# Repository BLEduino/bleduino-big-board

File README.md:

Big-Board
=========

The BLEduinos test board used to verify and test the individual components on the final BLEduino.

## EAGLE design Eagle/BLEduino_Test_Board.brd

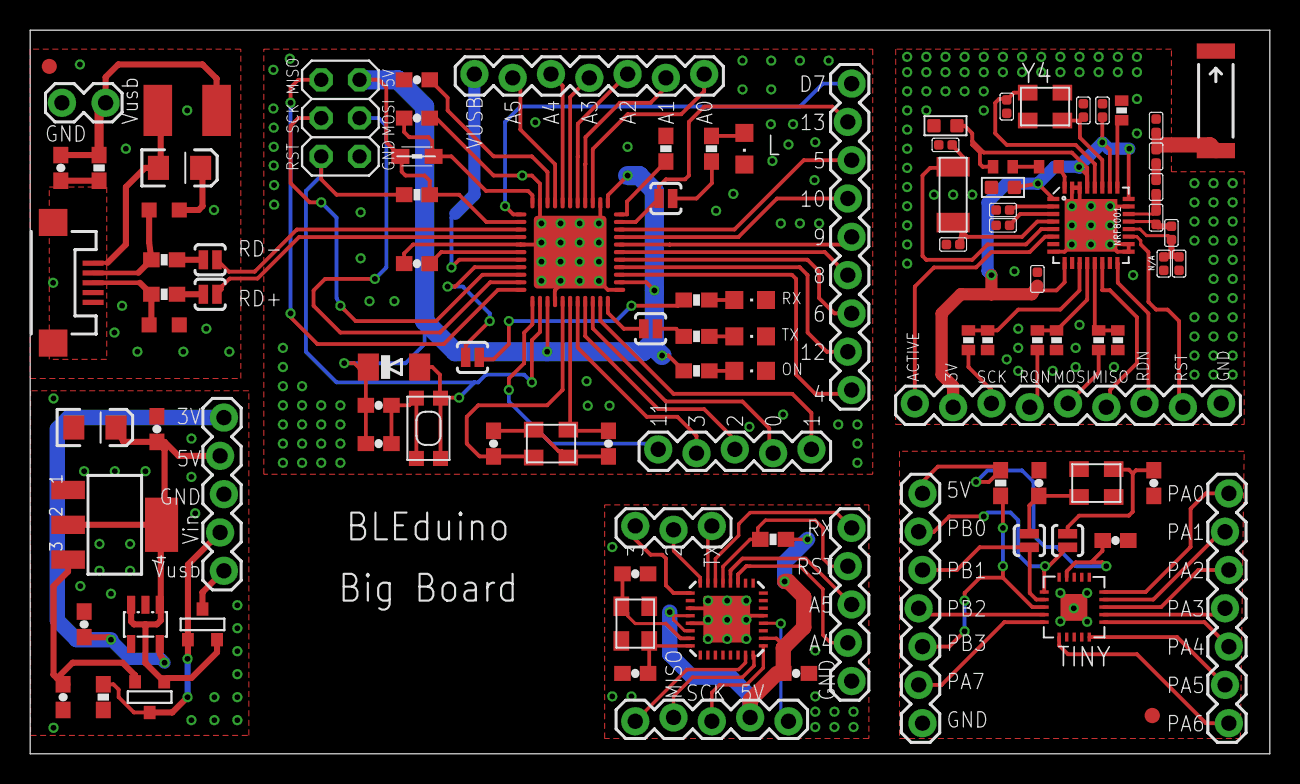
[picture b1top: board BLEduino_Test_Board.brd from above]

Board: 4 copper layers, 82.2 x 48.0 mm, 103 parts (0 on the bottom side), 114 nets.

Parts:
32.768KHZ: FITNESSDEVICE_CRYSTAL-ABS10
C1, C2, C6, C9, C10, C11, C32: 100n; 0603-CAP
C3, C14: 22u; EIA3216
C4, C5, C7: 1uF; 0603-CAP
C8, C12, C13, C15, C19, C30, C31: 22pF; 0603-CAP
C16, C24: 1uF; C0603
C17: 33nF; C0402
C18, C22: 100nF; C0402
C20, C21: 15pF; C0402
C23: 2.2nF; C0402
C25: 1.8pF; C0402
C26: 1.2pF; C0402
C27: 1nF; C0402
C28, C29: 12pF; C0402
D2: CD1206-S01575; MINIMELF
F1: MF-MSMF050-2 500mA; L1812
J4: 3x2M; 2X03
JP1, JP8, JP9, JP11: 1X05_LOCK
JP2: 1X02_LOCK
JP3, JP5, JP7: 1X07_LOCK
JP6: 1X03_LOCK
JP10, JP12: M09LOCK; 1X09_LOCK
L: green; CHIPLED_0805
L1: 5.6nH; L0402
L2: MH2029-300Y; 0805
L3: 8.2nH; L0402
L4: 3.9nH; L0402
L5: 10uH; C0402
L6: 15nH; C0402
N/A: 0; C0402
NRF8001: FITNESSDEVICE_NRF8001; FITNESSDEVICE_QFN-32
ON: blue; CHIPLED_0805
R1, R2, R4, R9, R18, R19: 10K; 0603-RES
R3, R10: 22; 0603-RES
R5, R6, R7, R8: 1K; 0603-RES
R11: 22K; 0402-RES
R12, R14, R15: 10K; 0402-RES
R13, R16, R17: 20K; 0402-RES
RESET: SPST_TACT-KMR2; KMR2
RX: yellow; CHIPLED_0805
SJ1, SJ2, SJ3, SJ4, SJ5, SJ10, SJ11: SOLDERJUMPERNO; SJ_2S-NO
T1: FDN340P/PMV48XP; SOT-23
T2: PMV48XP; SOT-23
TINY: ATTINY84ATMEL; ATTINT84-QFN
TX: yellow; CHIPLED_0805
U1: ATMEGA32U4-XUMU; QFN44ML7X7
U2: NCP1117-5; LINEAR_SOT223
U4: LP2985-33DBVR; SOT23-DBV
U$8: ATMEL328-QFNATMEL328; QFN
U$10: ANTENNA2SMD5; ANTENNA-CHIP5
U$37: FIDUCIALMOUNT; FIDUCIA-MOUNT
U$53: FIDUCIAL1X2; FIDUCIAL-1X2
X1: USB-MICROB
Y1, Y2, Y3, Y4: 16MHz KX-7; CRYSTAL-3.2-2.5
Z1, Z2: CG0603MLC-05E; CT/CN0603

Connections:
+5V: C10.1, C11.1, D2.C, J4.2, L2.1, R1.1, R5.1, U1.2, U1.14, U1.24, U1.34
+VIN: C1.1, T2.2, U2.3
A0: JP7.7, U1.36
A1: JP7.6, U1.37
A2: JP7.5, U1.38
A3: JP7.4, U1.39
A4: JP7.3, U1.40
A5: JP7.2, U1.41
ACTIVE: JP10.1, NRF8001.6
AREF: C6.1, U1.42
AVCC: C7.1, L2.2, U1.44
BIG_5V: C19.1, JP9.2, R18.1, U$8.AVCC, U$8.VCC, U$8.VCC2
BIG_A4: JP8.4, U$8.PC4
BIG_A5: JP8.3, U$8.PC5
BIG_AREF: JP9.1, U$8.AREF
BIG_D2: JP6.2, U$8.PD2
BIG_D3: JP6.1, U$8.PD3
BIG_GND: C8.1, C15.1, C19.2, JP8.5, U$8.GND, U$8.GND2, U$8.GND3, U$8.THERMAL_DIE, Y1.2, Y1.4
BIG_PB3_MISO: JP9.4, U$8.PB4
BIG_PB3_MOSI: JP9.5, U$8.PB3
BIG_PB3_SCK: JP9.3, U$8.PB5
BIG_RESET: JP8.2, R18.2, U$8.PC6
BIG_RX: JP8.1, U$8.PD0
BIG_TX: JP6.3, U$8.PD1
BLE_3V3: C16.1, C22.2, C24.1, C27.1, JP10.2, L6.2, NRF8001.1, NRF8001.9, NRF8001.24, NRF8001.26, NRF8001.29
BLE_GND: C16.2, C17.2, C18.2, C20.2, C21.2, C22.1, C23.1, C24.2, C26.2, C27.2, C28.2, C29.2, JP10.9, N/A.1, NRF8001.8, NRF8001.17, NRF8001.18, NRF8001.23, NRF8001.30, NRF8001.31, NRF8001.EP, R11.2, R13.1, R16.1, R17.1, Y4.1, Y4.3
BLE_MISO: JP10.6, NRF8001.14
BLE_MOSI: JP10.5, R15.1
BLE_MOSI_SHIFTED: NRF8001.13, R15.2, R17.2
BLE_RDNY: JP10.7, NRF8001.16
BLE_REQN: JP10.4, R14.1
BLE_REQN_SHIFTED: NRF8001.12, R14.2, R16.2
BLE_RESET: JP10.8, NRF8001.19
BLE_SCK: JP10.3, R12.1
BLE_SCK_SHIFTED: NRF8001.11, R12.2, R13.2
D0/RX: JP11.4, U1.20
D1/TX: JP11.5, U1.21
D2/SDA: JP11.3, U1.19
D3/SCL: JP11.2, U1.18
D4*: JP12.9, U1.25
D5*: JP12.3, U1.31
D6*: JP12.7, U1.27
D7: JP12.1, U1.1
D+: R10.2, X1.D+, Z1.1
D-: R3.2, X1.D-, Z2.1
GND: C5.2, C6.2, C7.2, C10.2, C11.2, C12.1, C13.1, J4.6, L.C, ON.C, R4.2, RESET.2, RESET.4, RX.C, TX.C, U1.5, U1.15, U1.23, U1.35, U1.43, U1.EXP, Y3.2, Y3.4
HWB: R4.1, U1.33
IO8: JP12.6, U1.28
IO9*: JP12.5, U1.29
IO10*: JP12.4, U1.30
IO11*: JP11.1, U1.12
IO12*: JP12.8, U1.26
IO13*: JP12.2, SJ2.1, U1.32
MISO: J4.1, U1.11
MOSI: J4.4, U1.10
unnamed: R7.1, SJ1.2
unnamed: R7.2, RX.A
unnamed: ON.A, R5.2
unnamed: R6.2, TX.A
unnamed: R8.1, SJ2.2
unnamed: R6.1, SJ3.2
unnamed: L.A, R8.2
unnamed: R3.1, SJ5.2
unnamed: R10.1, SJ4.2
unnamed: C8.2, U$8.PB6, Y1.1
unnamed: C15.2, U$8.PB7, Y1.3
unnamed: C18.1, NRF8001.2
unnamed: L5.1, NRF8001.32
unnamed: C30.1, SJ11.2, Y2.3
unnamed: L5.2, L6.1
unnamed: C17.1, NRF8001.3
unnamed: 32.768KHZ.P$1, C20.1, NRF8001.4
unnamed: 32.768KHZ.P$2, C21.1, NRF8001.5
unnamed: C23.2, L1.2, N/A.2, NRF8001.20
unnamed: L3.2, L4.1, NRF8001.22
unnamed: L1.1, L3.1, NRF8001.21
unnamed: C25.2, L4.2
unnamed: C25.1, C26.1, U$10.FEED
unnamed: NRF8001.25, R11.1
unnamed: C28.1, NRF8001.28, Y4.4
unnamed: C29.1, NRF8001.27, Y4.2
unnamed: C31.1, SJ10.1, Y2.1
PWR_3V3: C4.1, JP1.1, U4.5
PWR_5V: C2.1, C3.A, JP1.2, T1.2, T2.3, U2.2, U2.4, U4.1, U4.3
PWR_GND: C1.2, C2.2, C3.C, C4.2, JP1.3, R9.1, U2.1, U4.2
PWR_VIN: JP1.4, R9.2, T1.3, T2.1
PWR_VUSB: JP1.5, T1.1
RD_N: SJ5.1, U1.3
RD_P: SJ4.1, U1.4
RESET: D2.A, J4.5, R1.2, RESET.1, RESET.3, U1.13
RXLED/SS: SJ1.1, U1.8
SCK: J4.3, U1.9
TINY_5V: C32.2, JP5.1, R19.2, TINY.VCC
TINY_GND: C30.2, C31.2, C32.1, JP5.7, TINY.EGND, TINY.GND, Y2.4
TINY_PA0: JP3.1, TINY.PA0
TINY_PA1: JP3.2, TINY.PA1
TINY_PA2: JP3.3, TINY.PA2
TINY_PA3: JP3.4, TINY.PA3
TINY_PA4: JP3.5, TINY.PA4
TINY_PA5: JP3.6, TINY.PA5
TINY_PA6: JP3.7, TINY.PA6
TINY_PA7: JP5.6, TINY.PA7
TINY_PB0: JP5.2, SJ10.2, TINY.PB0
TINY_PB1: JP5.3, SJ11.1, TINY.PB1
TINY_PB2: JP5.4, TINY.PB2
TINY_PB3: JP5.5, R19.1, TINY.PB3
TXLED: SJ3.1, U1.22
UCAP: C5.1, U1.6
USB_GND: C9.2, C14.A, JP2.1, R2.1, X1.GND, Z1.2, Z2.2
USB_VUSB: C9.1, F1.2, JP2.2, R2.2
VUSB: JP7.1, U1.7
VUSBD: C14.C, F1.1, X1.VBUS
XTAL1: C13.2, U1.17, Y3.3
XTAL2: C12.2, U1.16, Y3.1

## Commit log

2013-10-08 Added the missing files
